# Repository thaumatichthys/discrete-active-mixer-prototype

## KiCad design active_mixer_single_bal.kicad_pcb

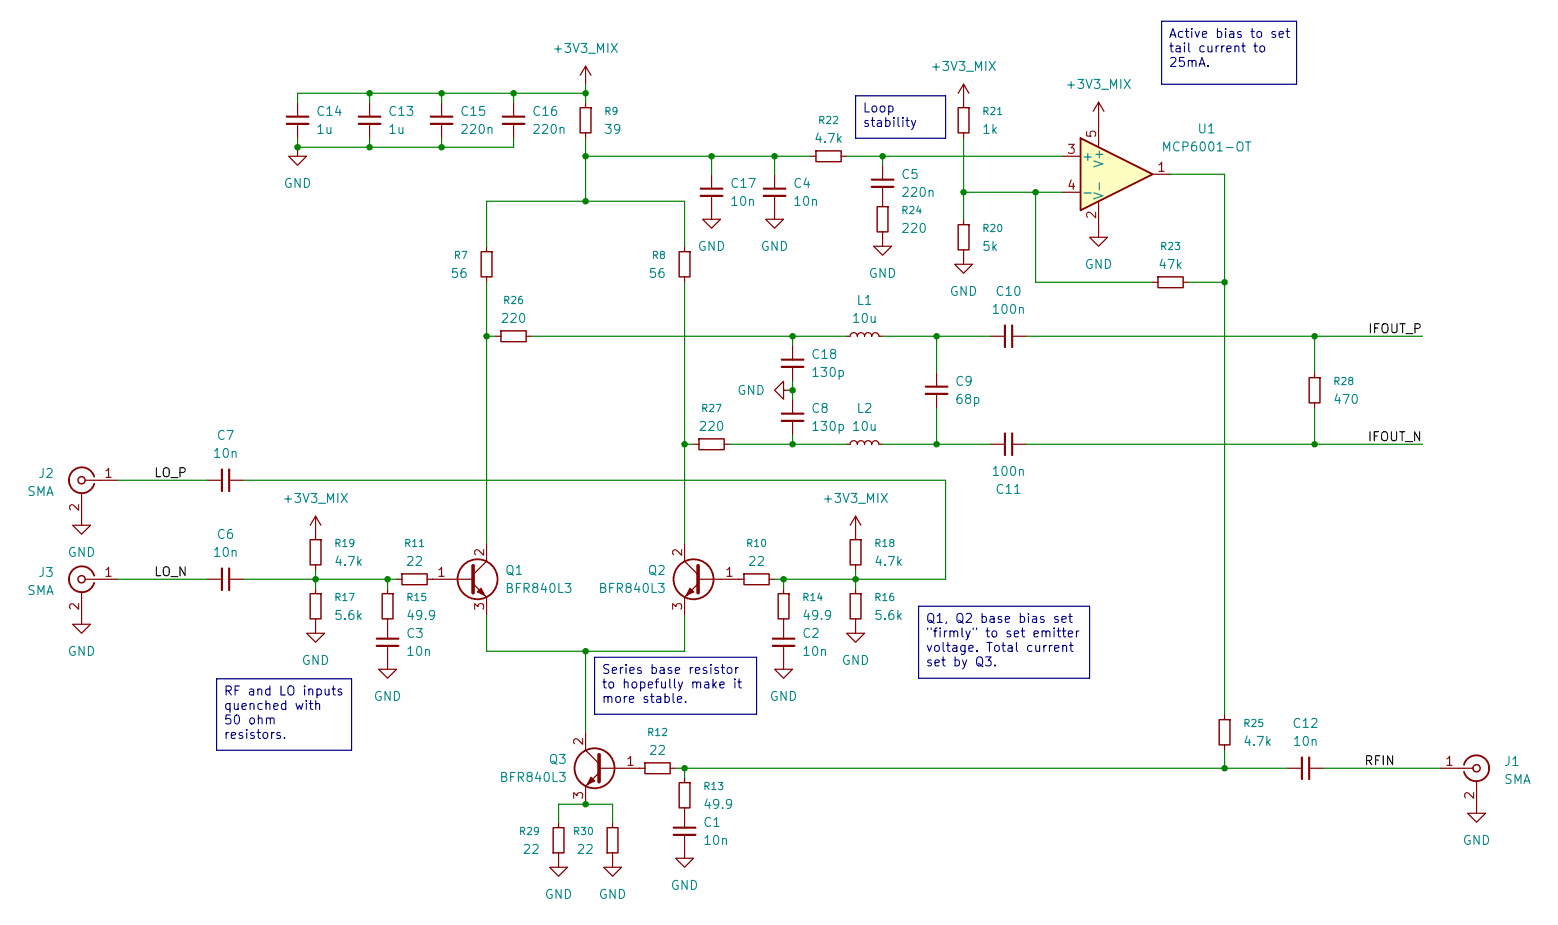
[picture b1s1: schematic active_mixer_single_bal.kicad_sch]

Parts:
C1, C2, C3, C4, C6, C7, C12, C17: 10n; C_0201_0603Metric
C5, C15, C16: 220n; C_0402_1005Metric
C8, C18: 130p; C_0402_1005Metric
C9: 68p; C_0402_1005Metric
C10, C11: 100n; C_0402_1005Metric
C13, C14: 1u; C_0603_1608Metric
J1, J2, J3: SMA; ADAMTECH_RF2-143-T-17-50-G_IMPROVED
L1, L2: 10u; L_0603_1608Metric
Q1, Q2, Q3: BFR840L3; SOT-883
R7, R8: 56; R_0201_0603Metric
R9: 39; R_0402_1005Metric
R10, R11, R12, R29, R30: 22; R_0201_0603Metric
R13, R14, R15: 49.9; R_0201_0603Metric
R16, R17: 5.6k; R_0201_0603Metric
R18, R19, R25: 4.7k; R_0201_0603Metric
R20: 5k; R_0402_1005Metric
R21: 1k; R_0402_1005Metric
R22: 4.7k; R_0402_1005Metric
R23: 47k; R_0402_1005Metric
R24: 220; R_0402_1005Metric
R26, R27: 220; R_0201_0603Metric
R28: 470; R_0201_0603Metric
U1: MCP6001-OT; SOT-23-5

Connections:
+3V3_MIX: C13.1, C14.1, C15.1, C16.1, R9.1, R18.1, R19.1, R21.1, U1.5 (V+)
/IFOUT_N: C11.2, R28.2
/IFOUT_P: C10.2, R28.1
/LO_N: C6.1, J3.1 (In)
/LO_P: C7.1, J2.1 (In)
/RFIN: C12.2, J1.1 (In)
GND: C1.2, C2.2, C3.2, C4.2, C8.1, C13.2, C14.2, C15.2, C16.2, C17.2, C18.2, J1.2 (Ext), J2.2 (Ext), J3.2 (Ext), R16.2, R17.2, R20.2, R24.2, R29.1, R30.1, U1.2 (V-)
unnamed: C1.1, R13.2
unnamed: C2.1, R14.2
unnamed: C3.1, R15.2
unnamed: C5.2, R24.1
unnamed: C6.2, R11.1, R15.1, R17.1, R19.2
unnamed: C7.2, R10.2, R14.1, R16.1, R18.2
unnamed: C8.2, L2.1, R27.2
unnamed: C9.1, C10.1, L1.2
unnamed: C9.2, C11.1, L2.2
unnamed: C12.1, R12.2, R13.1, R25.2
unnamed: C4.1, C17.1, R7.1, R8.1, R9.2, R22.1
unnamed: C18.1, L1.1, R26.2
unnamed: Q1.1 (B), R11.2
unnamed: Q1.2 (C), R7.2, R26.1
unnamed: Q1.3 (E), Q2.3 (E), Q3.2 (C)
unnamed: Q2.1 (B), R10.1
unnamed: Q2.2 (C), R8.2, R27.1
unnamed: Q3.1 (B), R12.1
unnamed: Q3.3 (E), R29.2, R30.2
unnamed: R23.2, R25.1, U1.1
unnamed: C5.1, R22.2, U1.3 (+)
unnamed: R20.1, R21.2, R23.1, U1.4 (-)

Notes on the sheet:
Active bias to set tail current to 25mA.
Q1, Q2 base bias set "firmly" to set emitter voltage. Total current set by Q3.
Series base resistor to hopefully make it more stable.
RF and LO inputs quenched with 50 ohm resistors.
Loop stability

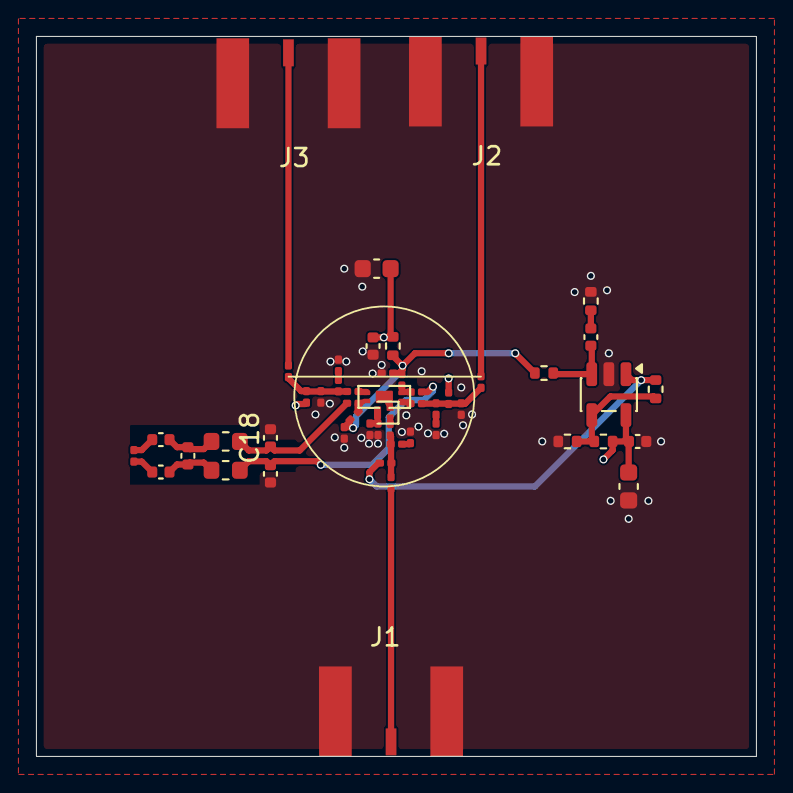
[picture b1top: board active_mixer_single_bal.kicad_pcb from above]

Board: 4 copper layers, 40.0 x 40.0 mm, 51 parts (0 on the bottom side), 29 nets.
